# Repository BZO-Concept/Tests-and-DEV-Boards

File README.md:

this repository contains all my test boards and many boards for developement Arduino or STM32. caution, use at own risks ; )

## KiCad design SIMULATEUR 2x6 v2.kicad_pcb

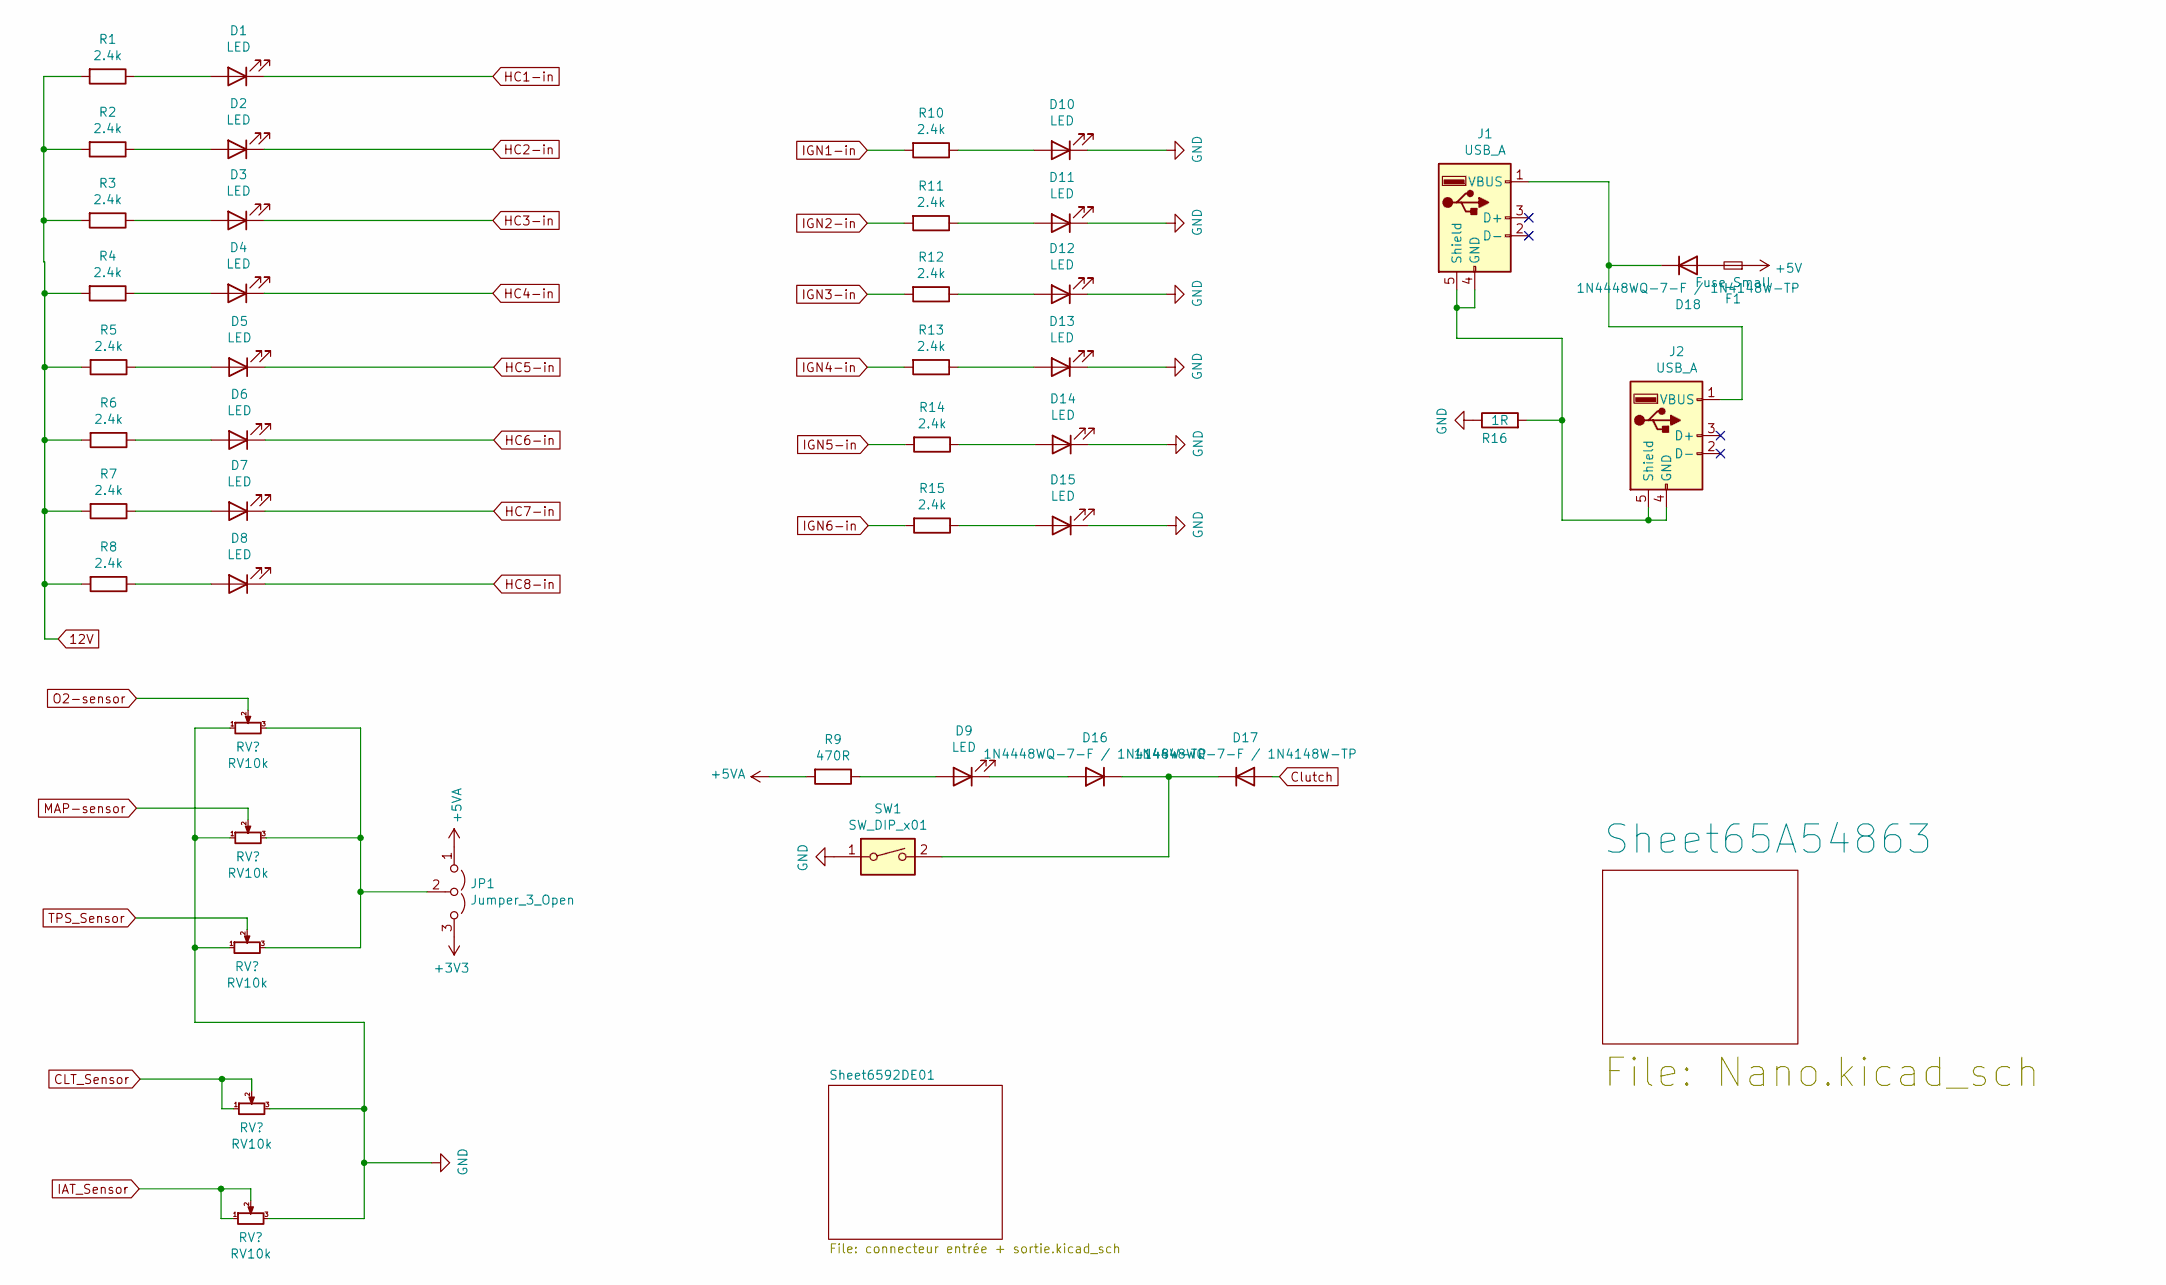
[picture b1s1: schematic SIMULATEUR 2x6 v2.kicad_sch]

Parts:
D1, D2, D3, D4, D5, D6, D7, D8, D9, D10, D11, D12, D13, D14, D15: LED; LED_1206_3216Metric_Pad1.42x1.75m_discret_HandSolder
D16, D17, D18: 1N4448WQ-7-F / 1N4148W-TP; D_SOD-123_Handsolder
F1: Fuse_Small; Fuse_2016_5041Metric
J1, J2: USB_A; USB_A_CONNFLY_DS1095-WNR0
JP1: Jumper_3_Open; PinHeader_1x03_P2.54mm_Vertical
R1, R2, R3, R4, R5, R6, R7, R8, R10, R11, R12, R13, R14, R15: 2.4k; R_0805_2012Metric_Pad1.20x1.40mm_HandSolder
R9: 470R; R_0805_2012Metric_Pad1.20x1.40mm_HandSolder
R16: 1R; R_0612_1632Metric_Pad1.18x3.40mm_HandSolder
RV1, RV2, RV3, RV4, RV5: RV10k; Potentiometer_Bourns_3314J_Vertical
SW1: SW_DIP_x01; SW_Push_SPST_NO_Alps_SKRK

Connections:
12V: R1.2, R2.2, R3.2, R4.2, R5.2, R6.2, R7.2, R8.2; also elsewhere on the board
+3V3: JP1.3 (B); also elsewhere on the board
+5V: F1.1; also elsewhere on the board
+5VA: JP1.1 (A), R9.2; also elsewhere on the board
CLT_Sensor: RV5.1, RV5.2; also elsewhere on the board
Clutch: D17.2 (A); also elsewhere on the board
GND: D10.1 (K), D11.1 (K), D12.1 (K), D13.1 (K), D14.1 (K), D15.1 (K), R16.1, RV1.1, RV2.1, RV3.1, RV4.3, RV5.3, SW1.1; also elsewhere on the board
HC1-in: D1.1 (K); also elsewhere on the board
HC2-in: D2.1 (K); also elsewhere on the board
HC3-in: D3.1 (K); also elsewhere on the board
HC4-in: D4.1 (K); also elsewhere on the board
HC5-in: D5.1 (K); also elsewhere on the board
HC6-in: D6.1 (K); also elsewhere on the board
HC7-in: D7.1 (K); also elsewhere on the board
HC8-in: D8.1 (K); also elsewhere on the board
IAT_Sensor: RV4.1, RV4.2; also elsewhere on the board
IGN1-in: R10.2; also elsewhere on the board
IGN2-in: R11.2; also elsewhere on the board
IGN3-in: R12.2; also elsewhere on the board
IGN4-in: R13.2; also elsewhere on the board
IGN5-in: R14.2; also elsewhere on the board
IGN6-in: R15.2; also elsewhere on the board
MAP-sensor: RV3.2; also elsewhere on the board
unnamed: D1.2 (A), R1.1
unnamed: D2.2 (A), R2.1
unnamed: D3.2 (A), R3.1
unnamed: D4.2 (A), R4.1
unnamed: D5.2 (A), R5.1
unnamed: D6.2 (A), R6.1
unnamed: D7.2 (A), R7.1
unnamed: D8.2 (A), R8.1
unnamed: D9.2 (A), R9.1
unnamed: D10.2 (A), R10.1
unnamed: D11.2 (A), R11.1
unnamed: D12.2 (A), R12.1
unnamed: D13.2 (A), R13.1
unnamed: D14.2 (A), R14.1
unnamed: D15.2 (A), R15.1
unnamed: D16.1 (K), D17.1 (K), SW1.2
unnamed: D9.1 (K), D16.2 (A)
unnamed: D18.1 (K), J1.1 (VBUS), J2.1 (VBUS)
unnamed: D18.2 (A), F1.2
unnamed: J1.4 (GND), J1.5 (Shield), J2.4 (GND), J2.5 (Shield), R16.2
unnamed: JP1.2 (C), RV1.3, RV2.3, RV3.3
O2-sensor: RV2.2; also elsewhere on the board
TPS_Sensor: RV1.2; also elsewhere on the board

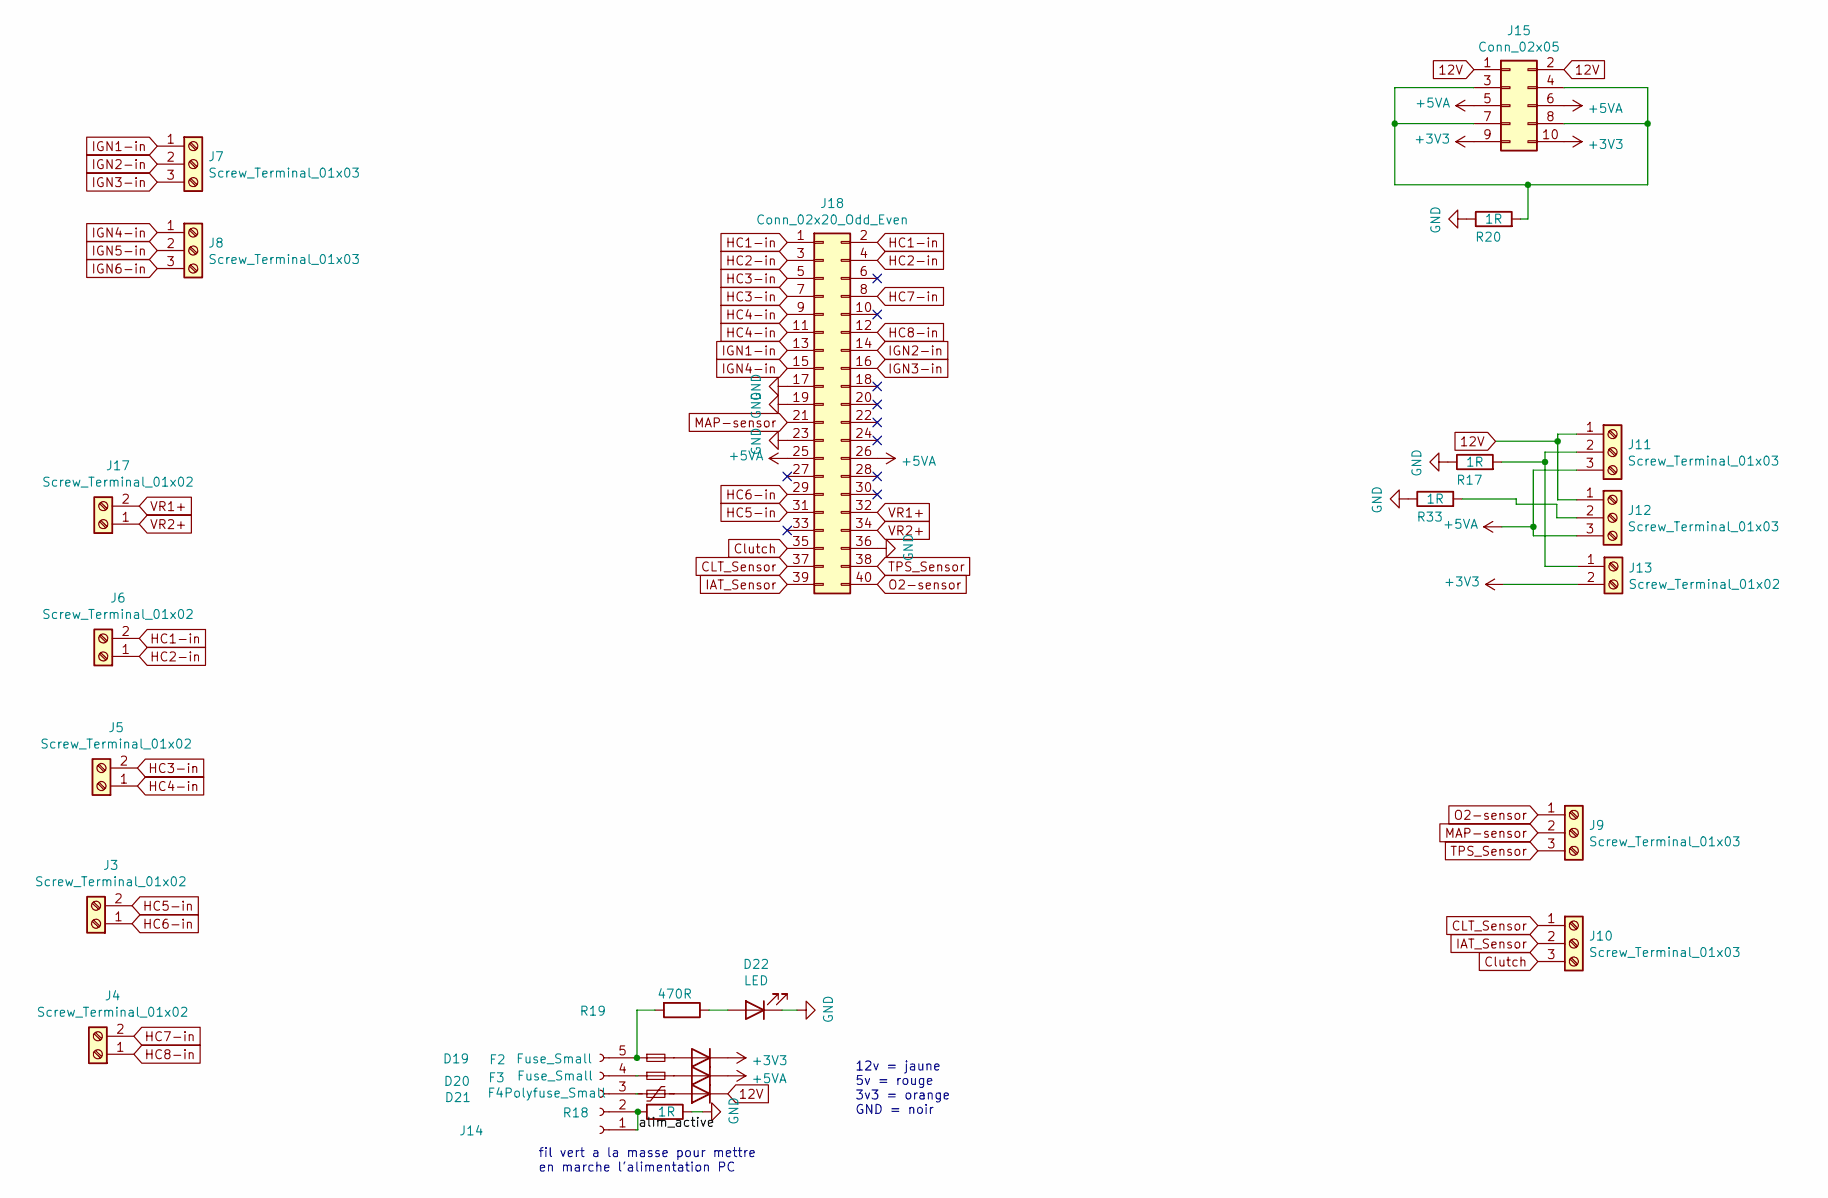
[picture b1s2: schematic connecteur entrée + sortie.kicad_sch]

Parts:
D19, D20, D21: 1N4448WQ-7-F / 1N4148W-TP; D_SOD-123_Handsolder
D22: LED; LED_1206_3216Metric_Pad1.42x1.75m_discret_HandSolder
F2, F3: Fuse_Small; Fuse_2016_5041Metric
F4: Polyfuse_Small; Fuse_2016_5041Metric
J3, J4, J5, J6, J13, J17: Screw_Terminal_01x02; TerminalBlock_bornier-2_P5.08mm
J7, J8, J9, J10, J11, J12: Screw_Terminal_01x03; TerminalBlock_bornier-3_P5.08mm
J14: Conn_01x05_Female; PinHeader_1x05_P2.54mm_Vertical
J15: Conn_02x05; PinHeader_2x05_P2.54mm_Vertical
J18: Conn_02x20_Odd_Even; IDC-Header_2x20_P2.54mm_Vertical
R17, R18, R20, R33: 1R; R_0612_1632Metric_Pad1.18x3.40mm_HandSolder
R19: 470R; R_0805_2012Metric_Pad1.20x1.40mm_HandSolder

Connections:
12V: D21.1 (K), J11.1, J12.1, J15.1, J15.2; also elsewhere on the board
+3V3: D19.1 (K), J13.2, J15.9, J15.10; also elsewhere on the board
+5VA: D20.1 (K), J11.3, J12.3, J15.5, J15.6, J18.25, J18.26; also elsewhere on the board
/Sheet6592DE01/alim_active: J14.1, J14.2, R18.2
CLT_Sensor: J10.1, J18.37; also elsewhere on the board
Clutch: J10.3, J18.35; also elsewhere on the board
GND: D22.1 (K), J18.17, J18.19, J18.23, J18.36, R17.1, R18.1, R20.1, R33.1; also elsewhere on the board
HC1-in: J6.2, J18.1, J18.2; also elsewhere on the board
HC2-in: J6.1, J18.3, J18.4; also elsewhere on the board
HC3-in: J5.2, J18.5, J18.7; also elsewhere on the board
HC4-in: J5.1, J18.9, J18.11; also elsewhere on the board
HC5-in: J3.2, J18.31; also elsewhere on the board
HC6-in: J3.1, J18.29; also elsewhere on the board
HC7-in: J4.2, J18.8; also elsewhere on the board
HC8-in: J4.1, J18.12; also elsewhere on the board
IAT_Sensor: J10.2, J18.39; also elsewhere on the board
IGN1-in: J7.1, J18.13; also elsewhere on the board
IGN2-in: J7.2, J18.14; also elsewhere on the board
IGN3-in: J7.3, J18.16; also elsewhere on the board
IGN4-in: J8.1, J18.15; also elsewhere on the board
IGN5-in: J8.2; also elsewhere on the board
IGN6-in: J8.3; also elsewhere on the board
MAP-sensor: J9.2, J18.21; also elsewhere on the board
unnamed: D19.2 (A), F2.2
unnamed: D20.2 (A), F3.2
unnamed: D21.2 (A), F4.1
unnamed: D22.2 (A), R19.1
unnamed: F2.1, J14.5, R19.2
unnamed: F3.1, J14.4
unnamed: F4.2, J14.3
unnamed: J11.2, J13.1, R17.2
unnamed: J12.2, R33.2
unnamed: J15.3, J15.4, J15.7, J15.8, R20.2
O2-sensor: J9.1, J18.40; also elsewhere on the board
TPS_Sensor: J9.3, J18.38; also elsewhere on the board
VR1+: J17.2, J18.32; also elsewhere on the board
VR2+: J17.1, J18.34; also elsewhere on the board

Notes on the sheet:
fil vert a la masse pour mettre en marche l'alimentation PC
12v = jaune 5v = rouge 3v3 = orange GND = noir

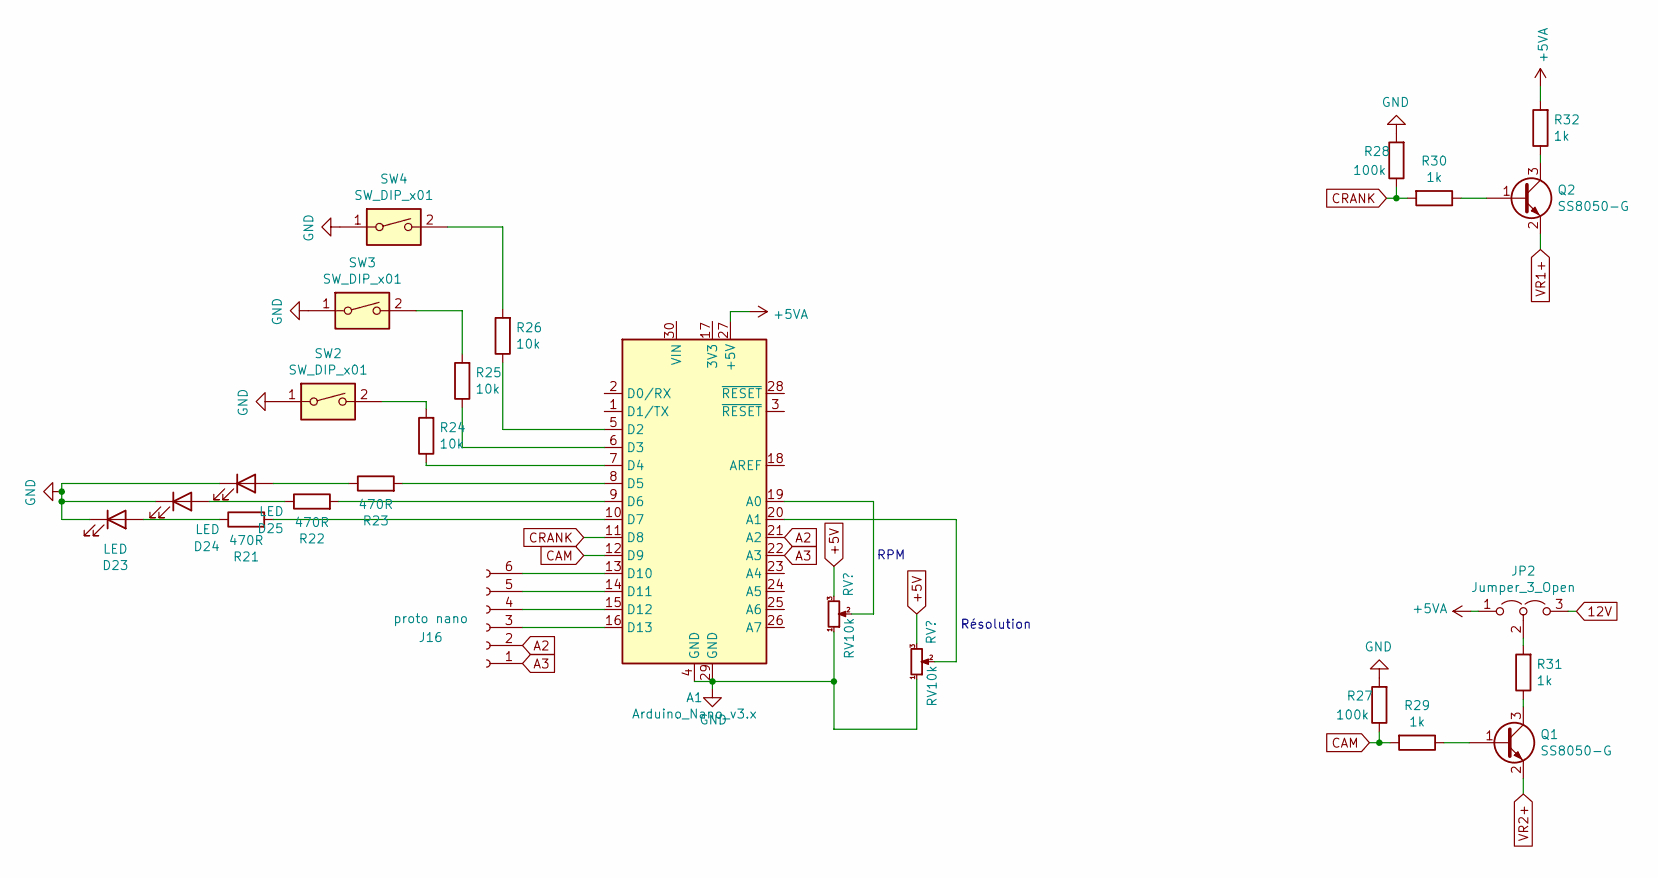
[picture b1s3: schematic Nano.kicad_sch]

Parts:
A1: Arduino_Nano_v3.x; Arduino_Nano
D23, D24, D25: LED; LED_1206_3216Metric_Pad1.42x1.75m_discret_HandSolder
J16: proto nano; PinHeader_1x06_P2.54mm_Vertical
JP2: Jumper_3_Open; PinHeader_1x03_P2.54mm_Vertical
Q1, Q2: SS8050-G; SOT-23
R21, R22, R23: 470R; R_0805_2012Metric_Pad1.20x1.40mm_HandSolder
R24, R25, R26: 10k; R_0805_2012Metric_Pad1.20x1.40mm_HandSolder
R27, R28: 100k; R_0805_2012Metric_Pad1.20x1.40mm_HandSolder
R29, R30, R31, R32: 1k; R_0805_2012Metric_Pad1.20x1.40mm_HandSolder
RV6, RV7: RV10k; Potentiometer_Bourns_3314J_Vertical
SW2, SW3, SW4: SW_DIP_x01; SW_Push_SPST_NO_Alps_SKRK

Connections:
12V: JP2.3 (B); also elsewhere on the board
+5V: RV6.3, RV7.3; also elsewhere on the board
+5VA: A1.27 (+5V), JP2.1 (A), R32.2; also elsewhere on the board
A2: A1.21 (A2), J16.2
A3: A1.22 (A3), J16.1
CAM: A1.12 (D9), R27.1, R29.2
CRANK: A1.11 (D8), R28.1, R30.2
GND: A1.4 (GND), A1.29 (GND), D23.1 (K), D24.1 (K), D25.1 (K), R27.2, R28.2, RV6.1, RV7.1, SW2.1, SW3.1, SW4.1; also elsewhere on the board
unnamed: A1.5 (D2), R26.1
unnamed: A1.6 (D3), R25.1
unnamed: A1.7 (D4), R24.1
unnamed: A1.8 (D5), R23.2
unnamed: A1.9 (D6), R22.2
unnamed: A1.10 (D7), R21.2
unnamed: A1.13 (D10), J16.6
unnamed: A1.14 (D11), J16.5
unnamed: A1.15 (D12), J16.4
unnamed: A1.16 (D13), J16.3
unnamed: A1.19 (A0), RV6.2
unnamed: A1.20 (A1), RV7.2
unnamed: D23.2 (A), R21.1
unnamed: D24.2 (A), R22.1
unnamed: D25.2 (A), R23.1
unnamed: JP2.2 (C), R31.2
unnamed: Q1.1 (B), R29.1
unnamed: Q1.3 (C), R31.1
unnamed: Q2.1 (B), R30.1
unnamed: Q2.3 (C), R32.1
unnamed: R24.2, SW2.2
unnamed: R25.2, SW3.2
unnamed: R26.2, SW4.2
VR1+: Q2.2 (E); also elsewhere on the board
VR2+: Q1.2 (E); also elsewhere on the board

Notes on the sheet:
Résolution
RPM

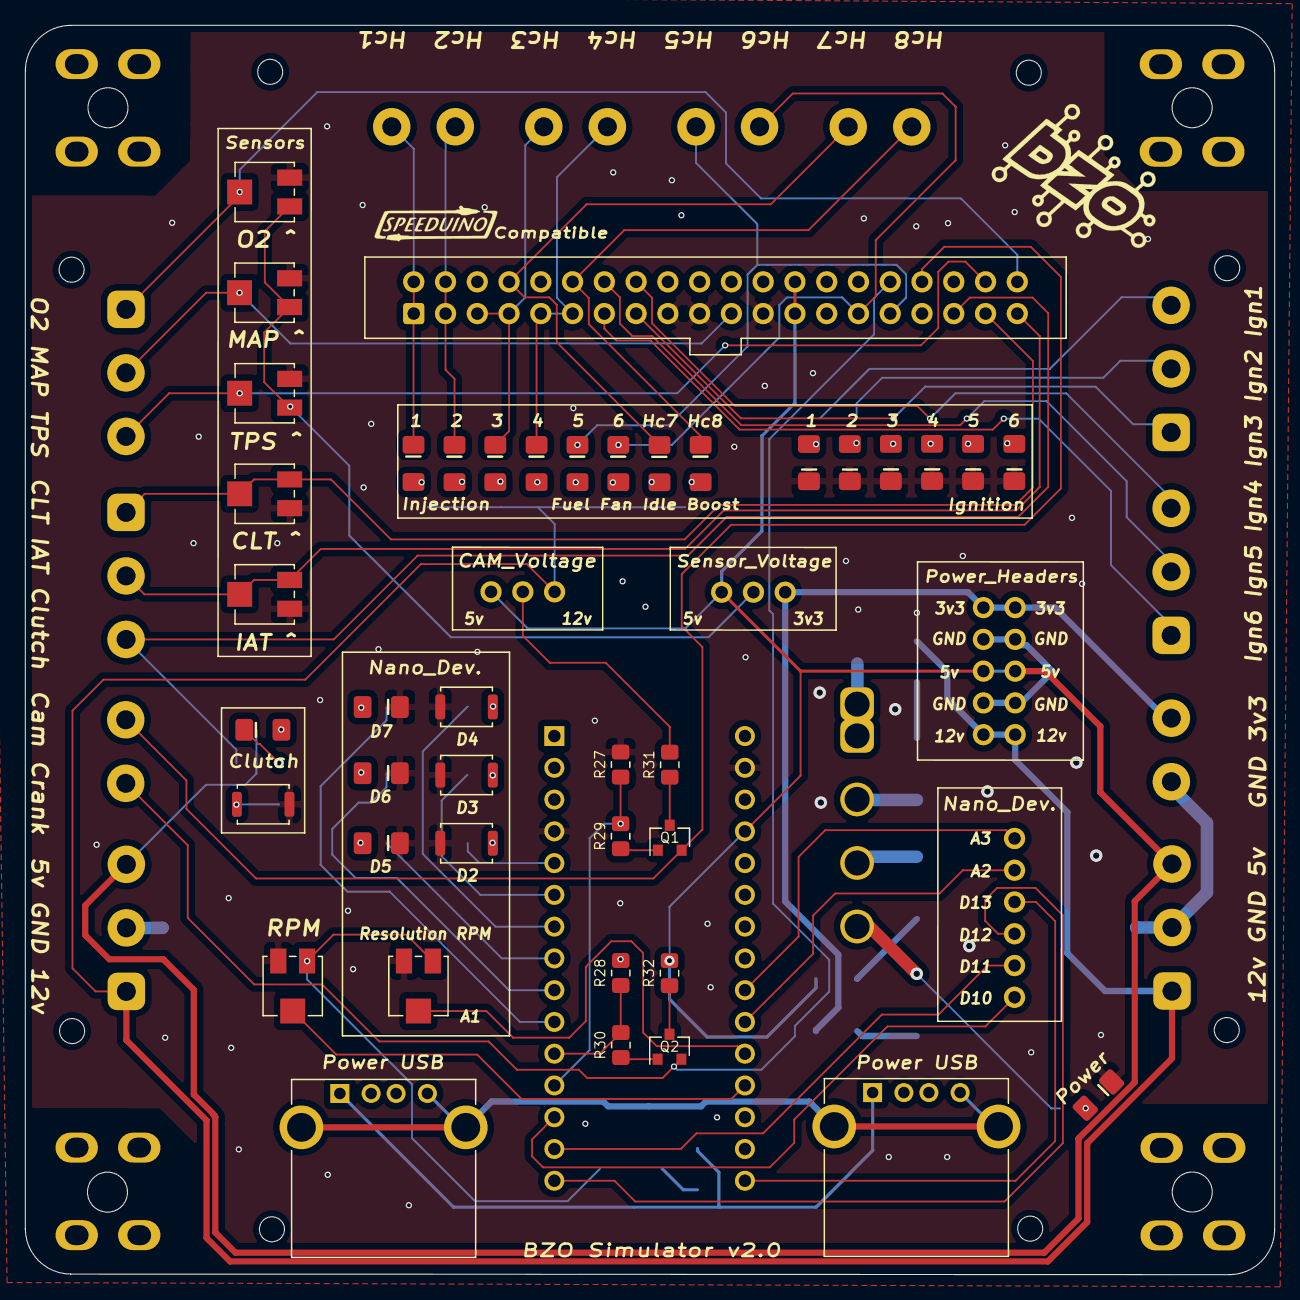
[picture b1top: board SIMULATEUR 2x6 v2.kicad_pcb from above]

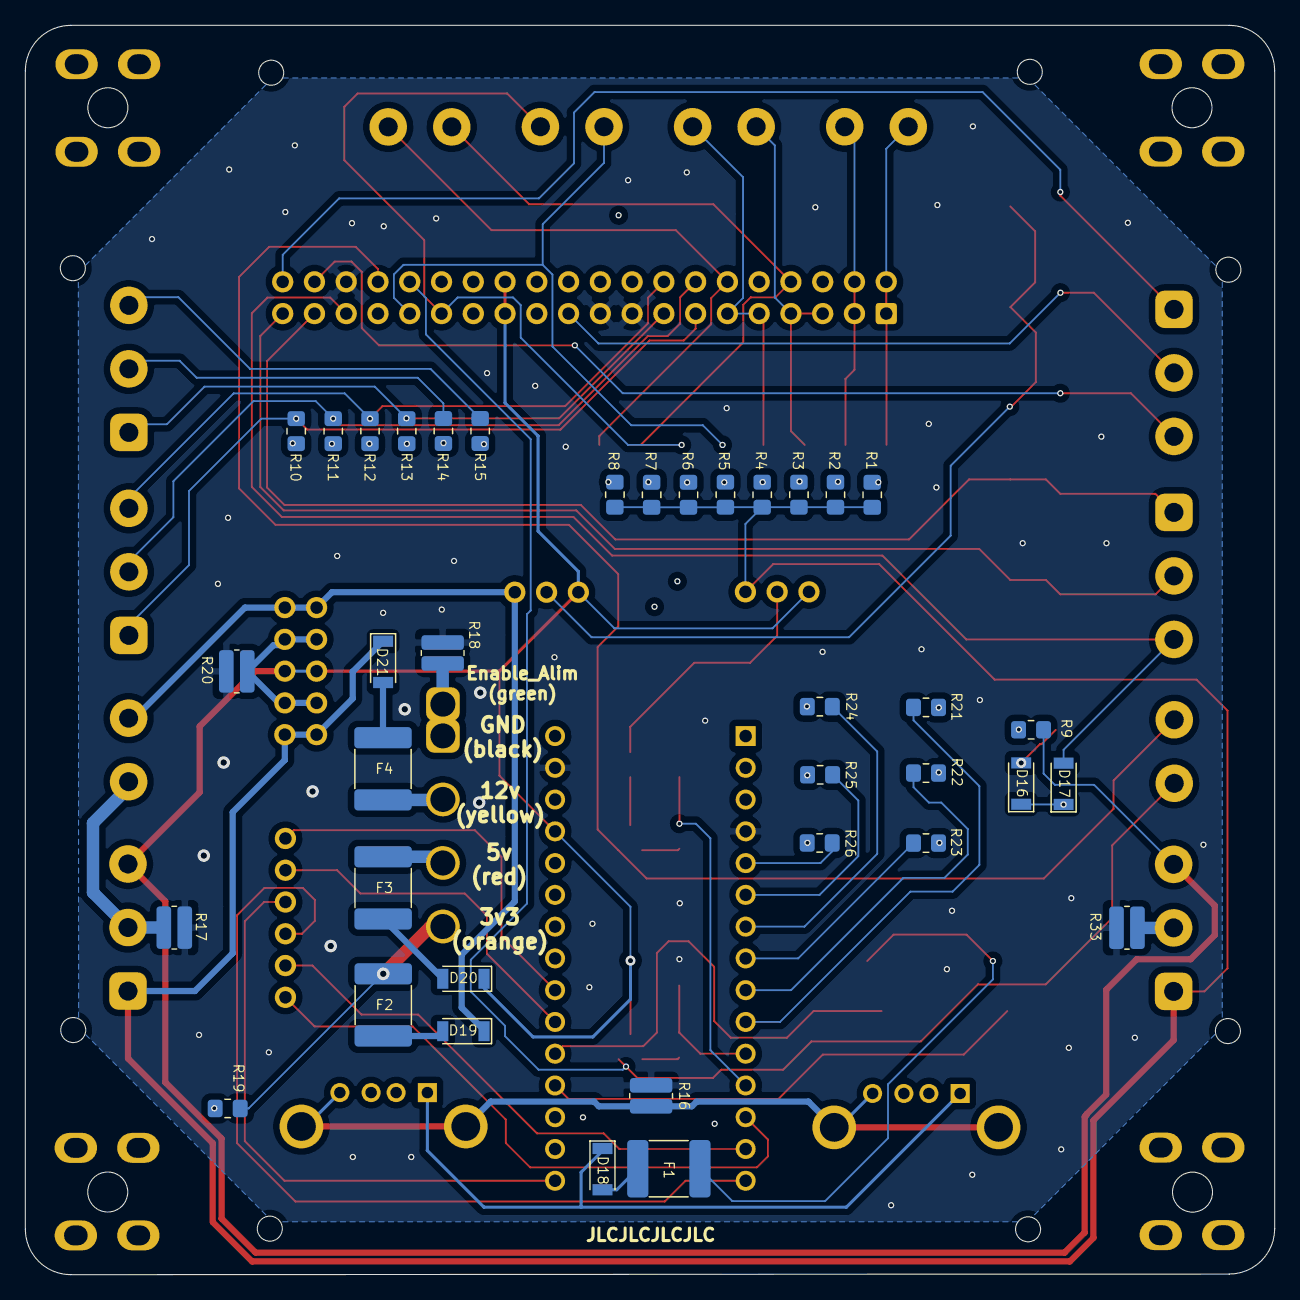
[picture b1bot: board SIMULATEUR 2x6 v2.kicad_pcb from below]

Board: 2 copper layers, 99.9 x 99.9 mm, 98 parts (37 on the bottom side), 86 nets.

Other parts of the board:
LOGO: LOGO; logo BZO
LOGO#2: LOGO; SPEEDUINO PETIT

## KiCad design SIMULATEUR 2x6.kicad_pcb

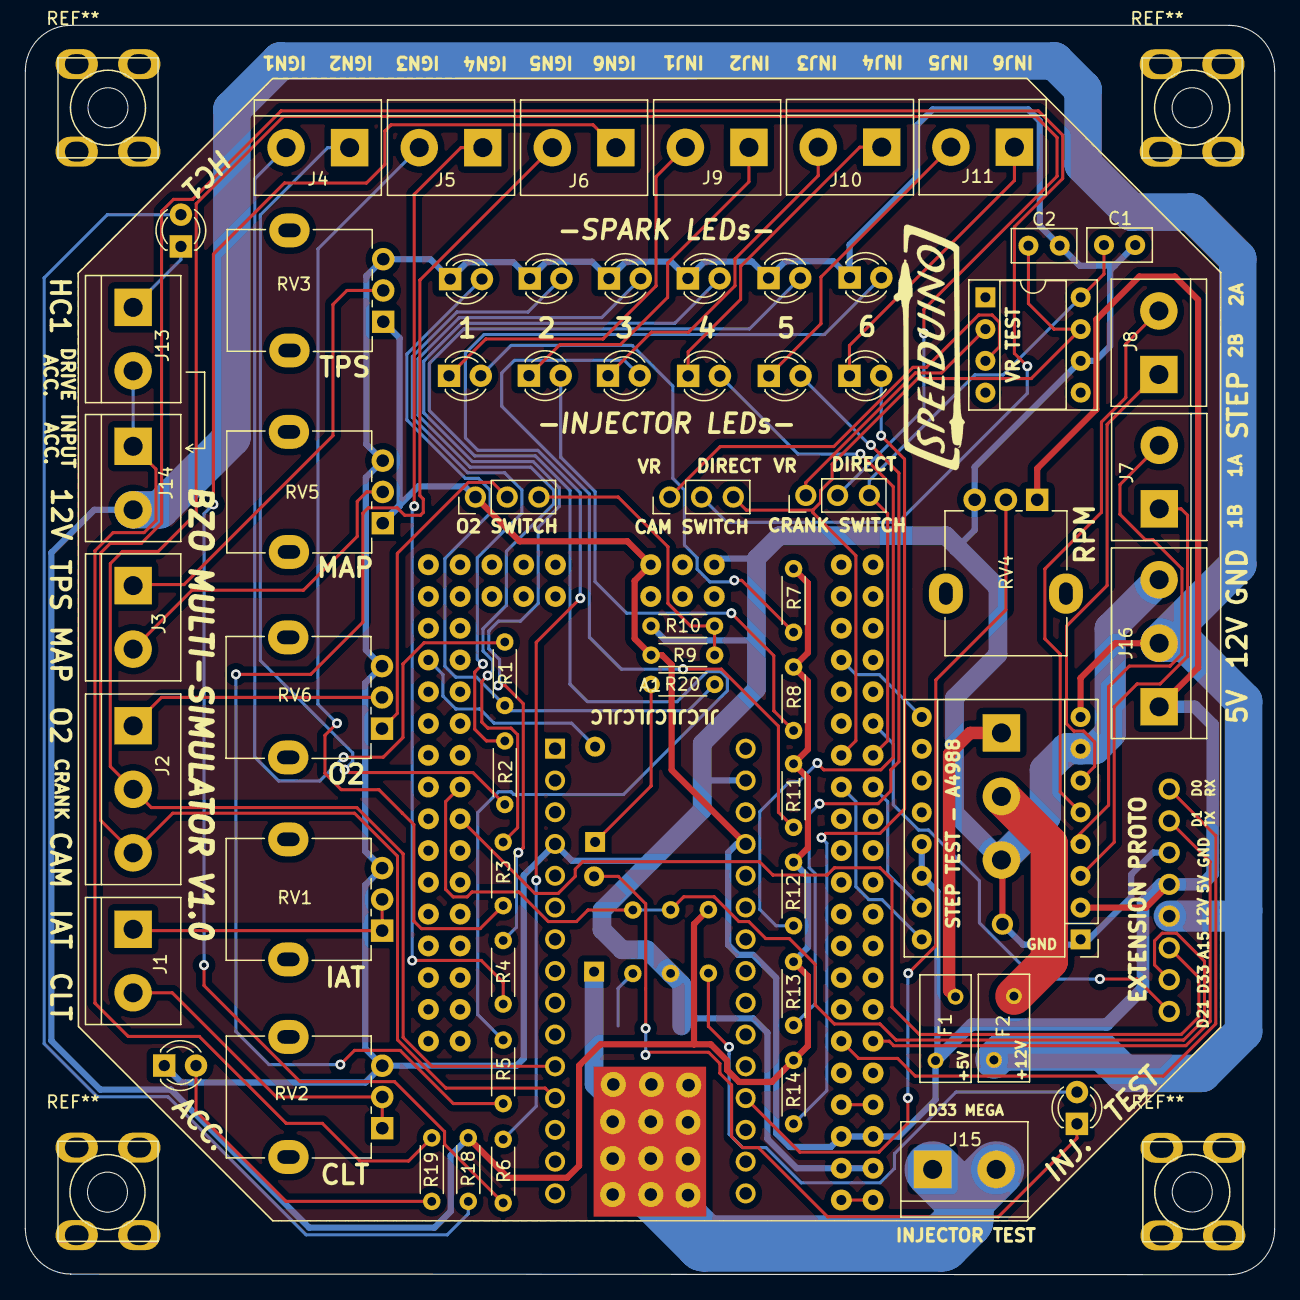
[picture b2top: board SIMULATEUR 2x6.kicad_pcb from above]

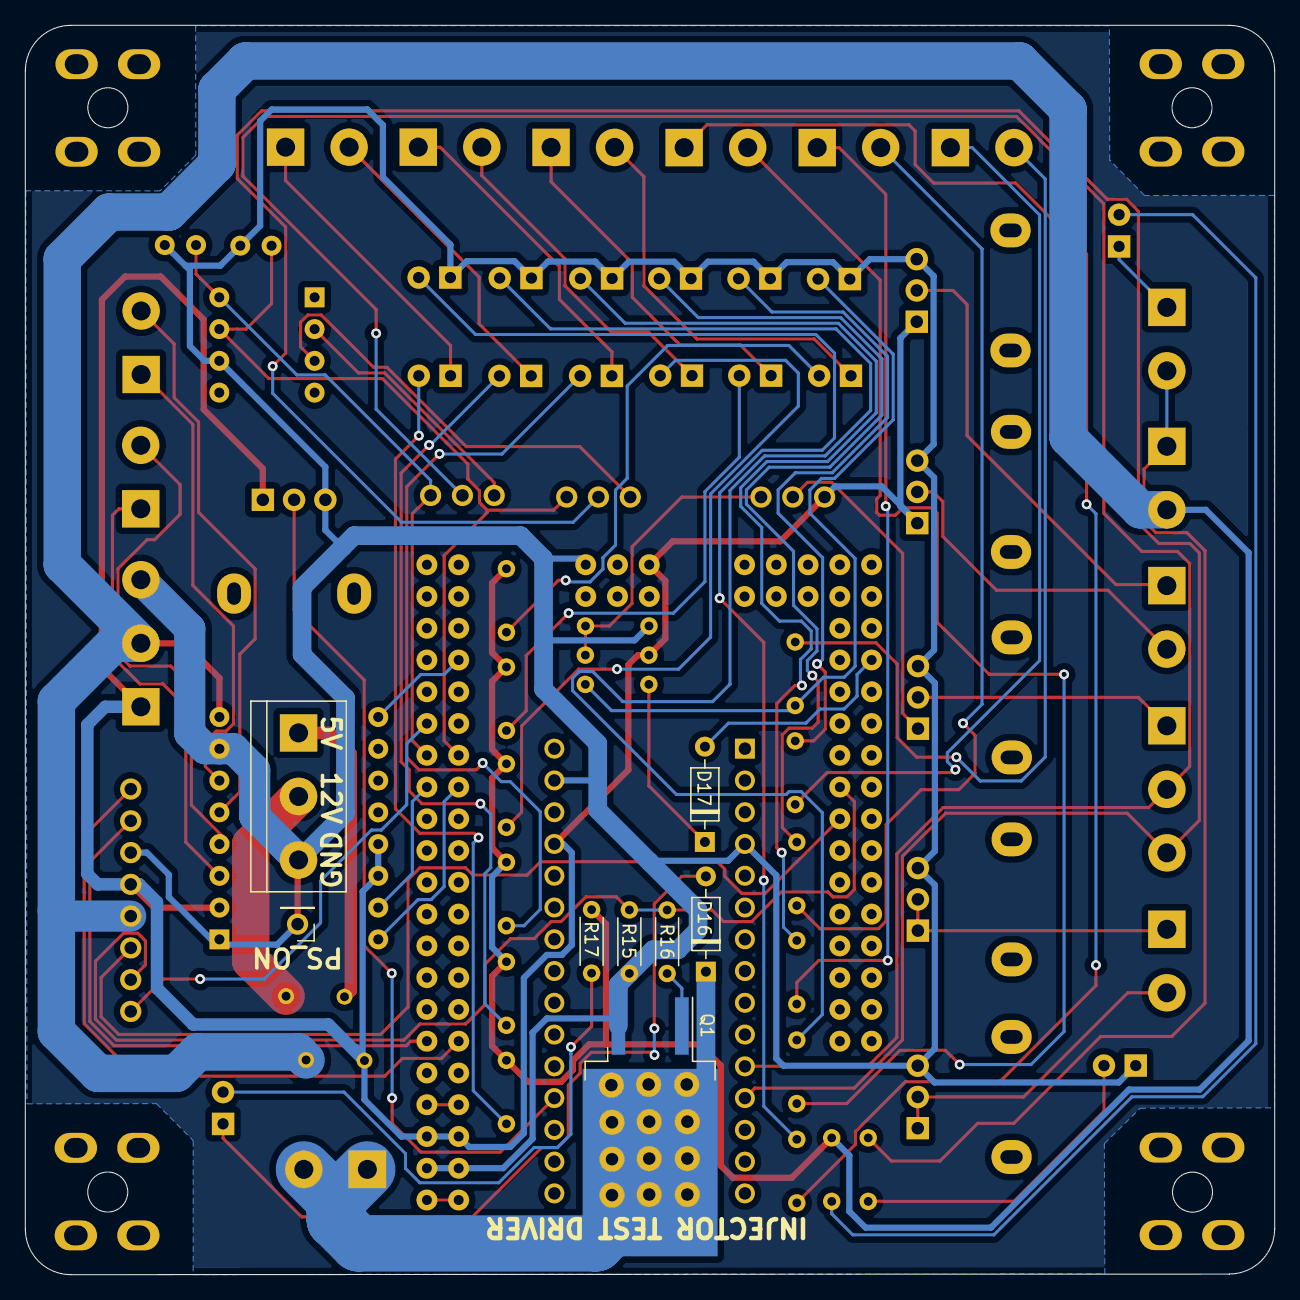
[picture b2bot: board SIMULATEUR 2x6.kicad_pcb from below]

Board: 2 copper layers, 99.9 x 99.9 mm, 73 parts (8 on the bottom side), 67 nets.

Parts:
A1: Arduino_Nano_v3.x; Arduino_Nano
A2: Pololu_Breakout_A4988; Pololu_Breakout-16_15.2x20.3mm
C1, C2: 0.01uF; C_Disc_D5.0mm_W2.5mm_P2.50mm
D1, D2, D3, D4, D5, D6, D7, D8, D9, D10, D11, D12, D13, D15: LED 3V; LED_D3.0mm
D14: LED; LED_D3.0mm
D16, D17: D; D_DO-35_SOD27_P7.62mm_Horizontal
F1: Fuse; Fuse_BelFuse_0ZRE0005FF_L8.3mm_W3.8mm
F2: POLYFUSE 3/5A; Fuse_BelFuse_0ZRE0005FF_L8.3mm_W3.8mm
IC1: Trig Cond Socket; DIP-8_W7.62mm_Socket
J1, J3, J4, J5, J6, J7, J8, J9, J10, J11, J13, J14, J15: Conn_01x02_Female; TerminalBlock_bornier-2_P5.08mm
J2, J16, J17: Conn_01x03_Female; TerminalBlock_bornier-3_P5.08mm
J12: Conn_01x06_Female; PinHeader_1x08_P2.54mm_Vertical
J18: PS_ON (GREEN or GREY); PinHeader_1x01_P2.54mm_Vertical
JP1, JP2: VR-HALL; PinHeader_1x03_P2.54mm_Vertical
JP3: Jumper_3_Bridged12; PinHeader_1x03_P2.54mm_Vertical
Q1: Q_NMOS_GDS; TO-263-2_COOLING_PAD
R1, R2, R3, R4, R5, R6, R10, R20: 100R; R_Axial_DIN0204_L3.6mm_D1.6mm_P5.08mm_Horizontal
R7, R8, R9, R11, R12, R13, R14, R18, R19: 470R; R_Axial_DIN0204_L3.6mm_D1.6mm_P5.08mm_Horizontal
R15: 100k; R_Axial_DIN0204_L3.6mm_D1.6mm_P5.08mm_Horizontal
R16: 1k; R_Axial_DIN0204_L3.6mm_D1.6mm_P5.08mm_Horizontal
R17: 2.4k; R_Axial_DIN0204_L3.6mm_D1.6mm_P5.08mm_Horizontal
RV1, RV2, RV3, RV4, RV5, RV6: R_POT 10k; Potentiometer_Alpha_RD901F-40-00D_Single_Vertical
U1: MEGA_PRO_EMBED_CH340G___ATMEGA2560; MODULE_MEGA_PRO_EMBED_CH340G___ATMEGA2560

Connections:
+5V: A1.27, A2.2, A2.13, A2.14, F1.1, J12.4, J16.1, JP3.1, R9.1, RV3.1, RV4.1, RV5.1, U1.5V_1, U1.5V_2, U1.5V_3
+12V: A2.8, F2.2, J12.5, J14.2, J16.2, R7.2, R8.2, R11.2, R12.2, R13.2, R14.2, R17.2, R18.2
CAM: A1.12, J2.3, JP2.2
CLT: J1.2, RV2.1, RV2.2
CRANK: A1.11, J2.2, JP1.2
Earth: A1.4, A1.29, A2.1, A2.7, C1.1, C2.1, D1.1, D2.1, D3.1, D4.1, D5.1, D6.1, D15.1, IC1.6, J12.3, J16.3, J17.3, J18.1, Q1.3, R10.2, R15.2, RV1.3, RV2.3, RV3.3, RV4.3, RV5.3, RV6.3, U1.GND_1, U1.GND_2, U1.GND_3
IAT: J1.1, RV1.1, RV1.2
MAP: J3.2, RV5.2
MCU-A15: J12.6, U1.A15
MCU-D16: A2.16, U1.D16
MCU-D17: A2.15, U1.D17
MCU-D18: C2.2, IC1.7, JP2.3, U1.D18
MCU-D19: C1.2, IC1.8, JP1.3, U1.D19
MCU-D21: J12.8, U1.D21
MCU-D24: A2.9, U1.D24
MCU-D33: J12.7, R15.1, R16.2, U1.D33
MCU-D40: D17.2, U1.D40
unnamed: A1.19, RV4.2
unnamed: D1.2, R1.2, R20.2
unnamed: D2.2, R2.2
unnamed: D3.2, R3.2
unnamed: D4.2, R4.2
unnamed: D5.2, R5.2
unnamed: D6.2, R6.2
unnamed: D7.1, J9.2
unnamed: D7.2, R7.1
unnamed: D8.1, J9.1
unnamed: D8.2, R8.1
unnamed: D9.1, J10.2
unnamed: D9.2, R11.1
unnamed: D10.1, J10.1
unnamed: D10.2, R12.1
unnamed: D11.1, J11.2
unnamed: D11.2, R13.1
unnamed: D12.1, J11.1
unnamed: D12.2, R14.1
unnamed: D13.1, J13.1
unnamed: D13.2, R18.1
unnamed: D14.1, D16.2
unnamed: D14.2, R17.1
unnamed: D15.2, R19.1
unnamed: D16.1, J15.1, J15.2, Q1.2
unnamed: D17.1, R20.1
unnamed: F1.2, J17.1
unnamed: F2.1, J17.2
unnamed: IC1.2, JP1.1
unnamed: IC1.3, JP2.1
unnamed: J4.1, R2.1
unnamed: J4.2, R1.1
unnamed: J5.1, R4.1
unnamed: J5.2, R3.1
unnamed: J6.1, R6.1
unnamed: J6.2, R5.1
unnamed: J13.2, J14.1, R19.2
unnamed: JP3.2, RV6.1
unnamed: JP3.3, R9.2, R10.1
unnamed: Q1.1, R16.1
unnamed: U1.3V3_1, U1.3V3_2
unnamed: U1.VIN_1, U1.VIN_2
O2: J2.1, RV6.2
RX0_D0: J12.1, U1.RX
STEP-1A: A2.4, J7.2
STEP-1B: A2.3, J7.1
STEP-2A: A2.5, J8.2
STEP-2B: A2.6, J8.1
TPS: J3.1, RV3.2
TX0_D1: J12.2, U1.TX

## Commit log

2024-06-14 Add files via upload
    the VR1 VR2 stimulator don't work with mosfets. use a external MIC4120 for VR2, direct without transistor for VR1
